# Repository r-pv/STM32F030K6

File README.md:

# rSTM32F030K6 ProMini

An ST development board based on the rSTM32F030K6T6/rSTM32F030K6 (Clock: 48MHz, flash: 32Kb, Ram:4Kb) MCU (LQFP-32) compatible with STM32Duino (Arduino).

## Install

**Update:** STCore v2.0 includes support for this MCU, if you're using STCore v2.0 you don't need to install anything.

- This requires the [STM32 core for arduino](https://github.com/stm32duino/Arduino_Core_STM32/), the ST original.
- I used this [guide to add the board](https://github.com/stm32duino/wiki/wiki/Add-a-new-variant-(board)), you can check it or continue with my suggestions to install the new board.
- Copy the **"DEMO_F030K6"** folder to the Arduino **"variants"** folder, in win7 is located at: **c:\Users\\<USERNAME\>\AppData\Local\Arduino15\packages\STM32\hardware\stm32\1.6.1\variants**
- Edit the **"boards.txt"** file, in win7 is located at a lever up than the "variants" folder, search for the **F030F4** board and add the lines to leave as I show you next:
```
# DEMO_F030F4 board
# Support: Serial1 (USART1 on PA3, PA2)
GenF0.menu.pnum.DEMO_F030F4=STM32F030F4 Demo board
GenF0.menu.pnum.DEMO_F030F4.upload.maximum_data_size=4096
GenF0.menu.pnum.DEMO_F030F4.upload.maximum_size=16384
GenF0.menu.pnum.DEMO_F030F4.build.mcu=cortex-m0
GenF0.menu.pnum.DEMO_F030F4.build.board=DEMO_F030F4
GenF0.menu.pnum.DEMO_F030F4.build.series=STM32F0xx
GenF0.menu.pnum.DEMO_F030F4.build.product_line=STM32F030x6
GenF0.menu.pnum.DEMO_F030F4.build.variant=DEMO_F030F4
GenF0.menu.pnum.DEMO_F030F4.build.cmsis_lib_gcc=arm_cortexM0l_math

# DEMO_F030K6 board
# Support: Serial1 (USART1 on PA3, PA2)
GenF0.menu.pnum.DEMO_F030K6=STM32F030K6 Demo board
GenF0.menu.pnum.DEMO_F030K6.upload.maximum_data_size=4096
GenF0.menu.pnum.DEMO_F030K6.upload.maximum_size=32768
GenF0.menu.pnum.DEMO_F030K6.build.mcu=cortex-m0
GenF0.menu.pnum.DEMO_F030K6.build.board=DEMO_F030K6
GenF0.menu.pnum.DEMO_F030K6.build.series=STM32F0xx
GenF0.menu.pnum.DEMO_F030K6.build.product_line=STM32F030x6
GenF0.menu.pnum.DEMO_F030K6.build.variant=DEMO_F030K6
GenF0.menu.pnum.DEMO_F030K6.build.cmsis_lib_gcc=arm_cortexM0l_math
```

## Files and Folders description

- **DEMO_F030K6** it's the variant board for the STM32 Arduino Core.
- **gerbers** it's the PCB gerbers.
- **rSTM32F030K6T6** it's the KiCAD 5.1.2 project.
- **Schematic.pdf** as in the name.

## Running some tests

## Reducing the size of your sketch

For some reason it seems that the sketchs for this platform gets way too fat (relative to standard arduino-atmel sketch sizes) and on some cases won't fit well on our board, a way to fit the sketchs to the flash/ram size that this board has it's to create a file **hal_conf_extra.h** on the sketch folder and disabling all features that weren't using:

```
#define HAL_ADC_MODULE_DISABLED
#define HAL_I2C_MODULE_DISABLED
#define HAL_RTC_MODULE_DISABLED
#define HAL_SPI_MODULE_DISABLED
#define HAL_TIM_MODULE_DISABLED
#define HAL_DAC_MODULE_DISABLED
#define HAL_EXTI_MODULE_DISABLED
#define HAL_ETH_MODULE_DISABLED
#define HAL_SD_MODULE_DISABLED
#define HAL_QSPI_MODULE_DISABLED
```
_(an arduino restart may be required on changes to this file)._

Also, if you aren't using the serial you cand disable it on the arduino menu:

**Board > U(S)ART Support > Disabled.**

## Notes

This it's the first board variant I made, so errors may occur.

[STM32Duino thread.](http://www.stm32duino.com/viewtopic.php?f=30&p=55201)

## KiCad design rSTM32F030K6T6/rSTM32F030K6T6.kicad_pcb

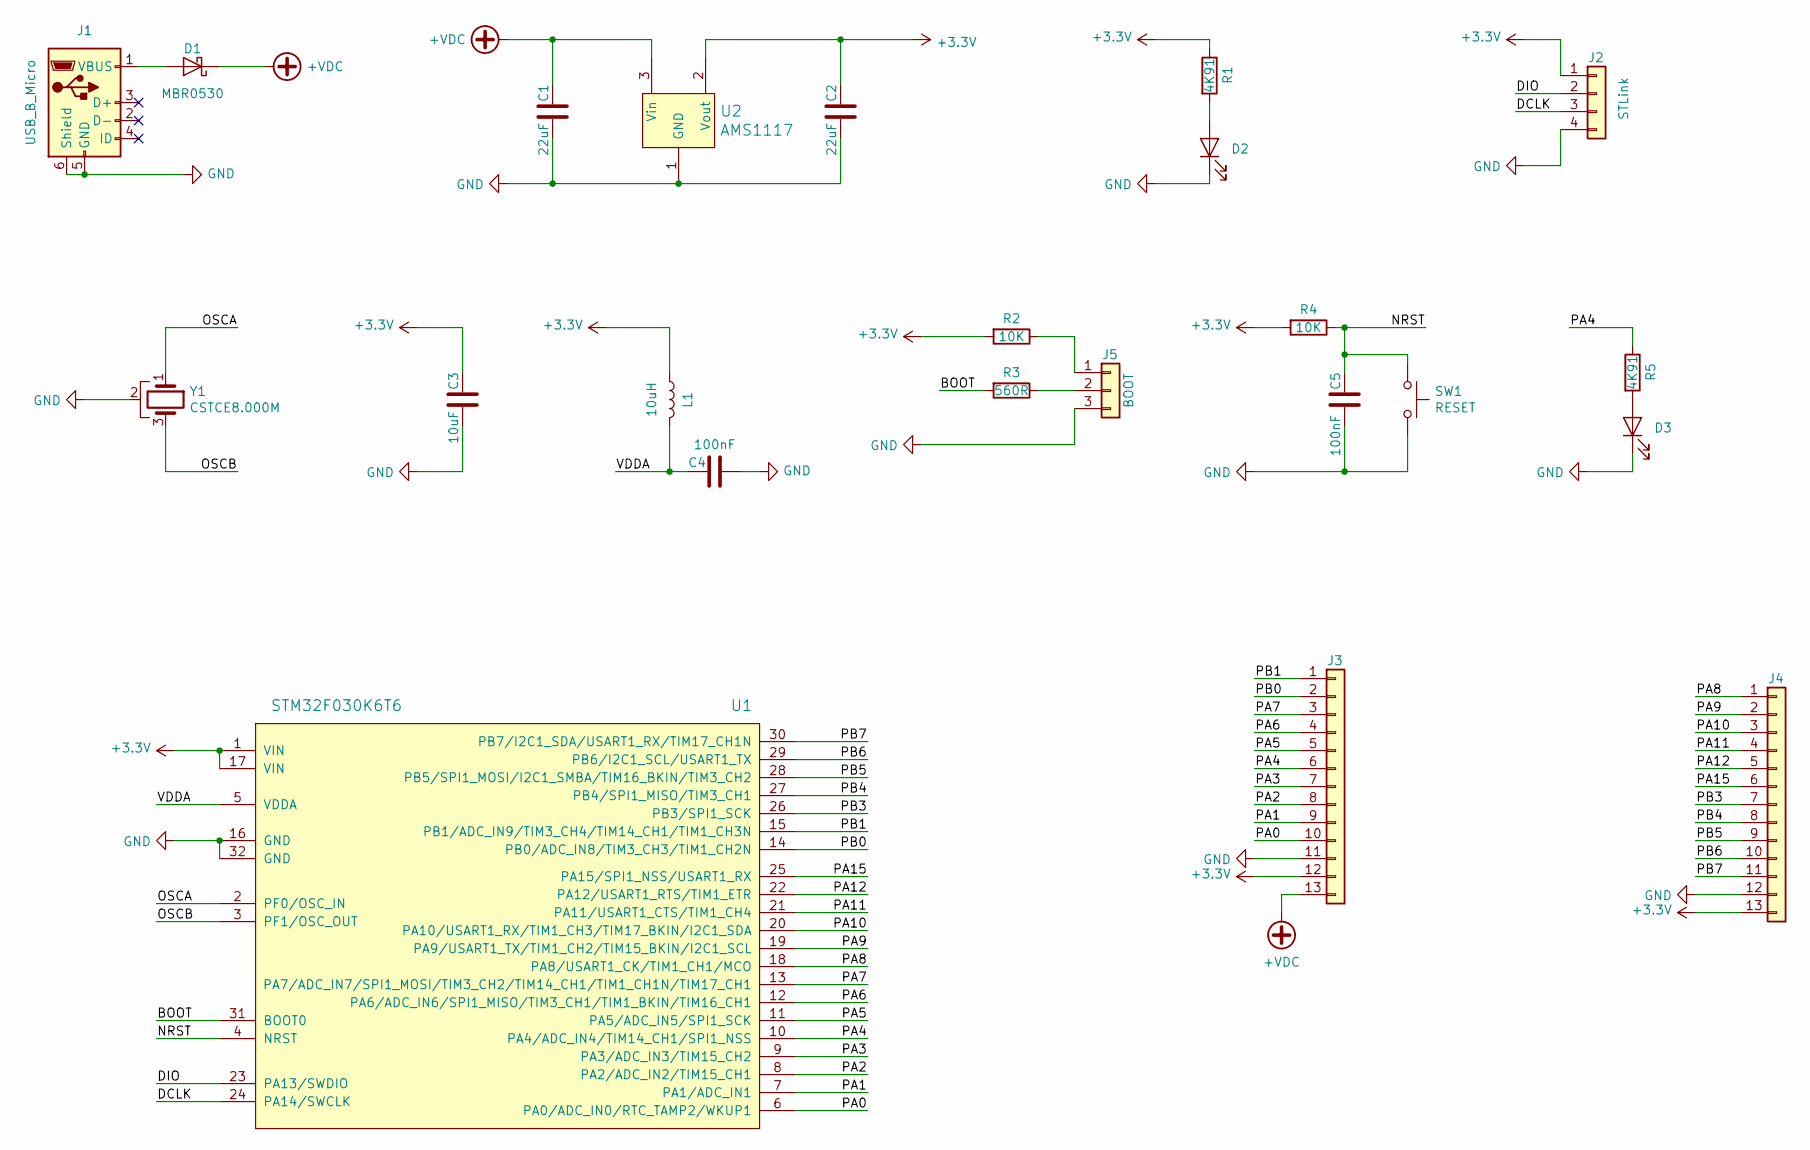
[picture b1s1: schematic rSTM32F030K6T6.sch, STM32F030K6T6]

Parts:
C1, C2: 22uF; C_0805
C3: 10uF; C_0805
C4, C5: 100nF; C_0805
D1: MBR0530; D_SOD-123
D2, D3: LED; LED_0805
J1: USB_B_Micro; USB_Micro-B_Molex_47346-0001
J2: STLink; Pin_Header_Straight_1x04_Pitch2.54mm
J3, J4: Pin_Header_Straight_1x13_Pitch2.54mm
J5: BOOT; Pin_Header_Straight_1x03_Pitch2.54mm
L1: 10uH; L_0805
R1, R5: 4K91; R_0603
R2, R4: 10K; R_0603
R3: 560R; R_0603
SW1: RESET; SW_SPST_EVPBF
U1: STM32F030K6T6; LQFP-32_7x7mm_Pitch0.8mm
U2: AMS1117; SOT-223-3_TabPin2
Y1: CSTCE8.000M; Crystal_CSTCE_3pin_3.2x1.3

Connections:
+3V3: C2.1, C3.1, J2.1, J3.12, J4.13, L1.1, R1.1, R2.2, R4.2, U1.1 (VIN), U1.17 (VIN), U2.2 (Vout)
+VDC: C1.1, D1.1 (K), J3.13, U2.3 (Vin)
/BOOT: R3.2, U1.31 (BOOT0)
/DCLK: J2.3, U1.24 (PA14/SWCLK)
/DIO: J2.2, U1.23 (PA13/SWDIO)
/NRST: C5.1, R4.1, SW1.1, U1.4 (NRST)
/OSCA: U1.2 (PF0/OSC_IN), Y1.1
/OSCB: U1.3 (PF1/OSC_OUT), Y1.3
/PA0: J3.10, U1.6 (PA0/ADC_IN0/RTC_TAMP2/WKUP1)
/PA1: J3.9, U1.7 (PA1/ADC_IN1)
/PA2: J3.8, U1.8 (PA2/ADC_IN2/TIM15_CH1)
/PA3: J3.7, U1.9 (PA3/ADC_IN3/TIM15_CH2)
/PA4: J3.6, R5.1, U1.10 (PA4/ADC_IN4/TIM14_CH1/SPI1_NSS)
/PA5: J3.5, U1.11 (PA5/ADC_IN5/SPI1_SCK)
/PA6: J3.4, U1.12 (PA6/ADC_IN6/SPI1_MISO/TIM3_CH1/TIM1_BKI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)
/PA7: J3.3, U1.13 (PA7/ADC_IN7/SPI1_MOSI/TIM3_CH2/TIM14_CH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)
/PA8: J4.1, U1.18 (PA8/USART1_CK/TIM1_CH1/MCO)
/PA9: J4.2, U1.19 (PA9/USART1_TX/TIM1_CH2/TIM15_BKIN/I2C1_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)
/PA10: J4.3, U1.20 (PA10/USART1_RX/TIM1_CH3/TIM17_BKIN/I2C1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)
/PA11: J4.4, U1.21 (PA11/USART1_CTS/TIM1_CH4)
/PA12: J4.5, U1.22 (PA12/USART1_RTS/TIM1_ETR)
/PA15: J4.6, U1.25 (PA15/SPI1_NSS/USART1_RX)
/PB0: J3.2, U1.14 (PB0/ADC_IN8/TIM3_CH3/TIM1_CH2N)
/PB1: J3.1, U1.15 (PB1/ADC_IN9/TIM3_CH4/TIM14_CH1/TIM1_CH3N)
/PB3: J4.7, U1.26 (PB3/SPI1_SCK)
/PB4: J4.8, U1.27 (PB4/SPI1_MISO/TIM3_CH1)
/PB5: J4.9, U1.28 (PB5/SPI1_MOSI/I2C1_SMBA/TIM16_BKIN/TIM3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)
/PB6: J4.10, U1.29 (PB6/I2C1_SCL/USART1_TX)
/PB7: J4.11, U1.30 (PB7/I2C1_SDA/USART1_RX/TIM17_CH1N)
/VDDA: C4.2, L1.2, U1.5 (VDDA)
GND: C1.2, C2.2, C3.2, C4.1, C5.2, D2.1 (K), D3.1 (K), J1.5 (GND), J1.6 (Shield), J2.4, J3.11, J4.12, J5.3, SW1.2, U1.16 (GND), U1.32 (GND), U2.1 (GND), Y1.2
unnamed: D1.2 (A), J1.1 (VBUS)
unnamed: D2.2 (A), R1.2
unnamed: D3.2 (A), R5.2
unnamed: J5.1, R2.1
unnamed: J5.2, R3.1

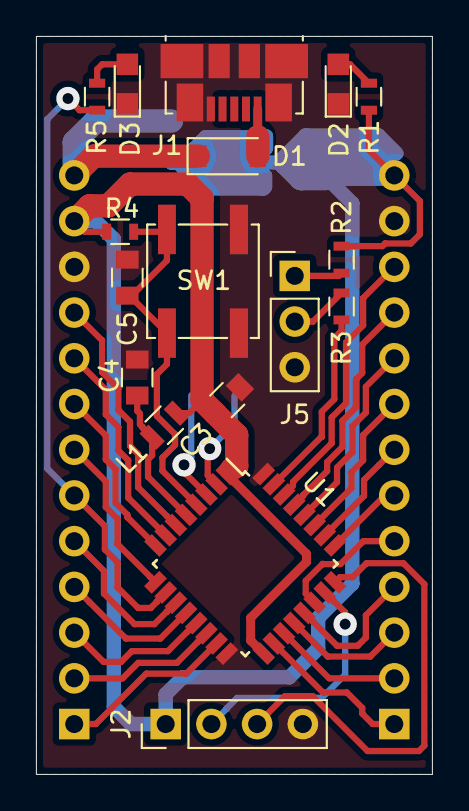
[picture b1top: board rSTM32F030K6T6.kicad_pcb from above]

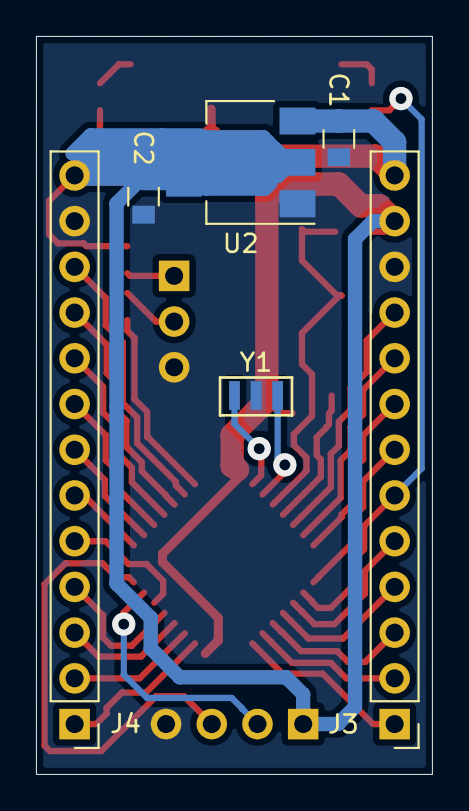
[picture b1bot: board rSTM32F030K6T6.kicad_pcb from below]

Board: 2 copper layers, 22.0 x 41.0 mm, 23 parts (6 on the bottom side), 36 nets.

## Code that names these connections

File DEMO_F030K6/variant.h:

/*
 *******************************************************************************
 * Copyright (c) 2017, STMicroelectronics
 * All rights reserved.
 *
 * Redistribution and use in source and binary forms, with or without
 * modification, are permitted provided that the following conditions are met:
 *
 * 1. Redistributions of source code must retain the above copyright notice,
 *    this list of conditions and the following disclaimer.
 * 2. Redistributions in binary form must reproduce the above copyright notice,
 *    this list of conditions and the following disclaimer in the documentation
 *    and/or other materials provided with the distribution.
 * 3. Neither the name of STMicroelectronics nor the names of its contributors
 *    may be used to endorse or promote products derived from this software
 *    without specific prior written permission.
 *
 * THIS SOFTWARE IS PROVIDED BY THE COPYRIGHT HOLDERS AND CONTRIBUTORS "AS IS"
 * AND ANY EXPRESS OR IMPLIED WARRANTIES, INCLUDING, BUT NOT LIMITED TO, THE
 * IMPLIED WARRANTIES OF MERCHANTABILITY AND FITNESS FOR A PARTICULAR PURPOSE ARE
 * DISCLAIMED. IN NO EVENT SHALL THE COPYRIGHT HOLDER OR CONTRIBUTORS BE LIABLE
 * FOR ANY DIRECT, INDIRECT, INCIDENTAL, SPECIAL, EXEMPLARY, OR CONSEQUENTIAL
 * DAMAGES (INCLUDING, BUT NOT LIMITED TO, PROCUREMENT OF SUBSTITUTE GOODS OR
 * SERVICES; LOSS OF USE, DATA, OR PROFITS; OR BUSINESS INTERRUPTION) HOWEVER
 * CAUSED AND ON ANY THEORY OF LIABILITY, WHETHER IN CONTRACT, STRICT LIABILITY,
 * OR TORT (INCLUDING NEGLIGENCE OR OTHERWISE) ARISING IN ANY WAY OUT OF THE USE
 * OF THIS SOFTWARE, EVEN IF ADVISED OF THE POSSIBILITY OF SUCH DAMAGE.
 *******************************************************************************
 */
#ifndef _VARIANT_ARDUINO_STM32_
#define _VARIANT_ARDUINO_STM32_

/*----------------------------------------------------------------------------
 *        Headers
 *----------------------------------------------------------------------------*/
#ifdef __cplusplus
extern "C"{
#endif // __cplusplus

/*----------------------------------------------------------------------------
 *        Pins
 *----------------------------------------------------------------------------*/
// USB connector on the top, MCU side
// Left.Side
#define PA0  0  //D0/A0
#define PA1  1  //D1/A1
#define PA2  2  //D2/A2 - TX
#define PA3  3  //D3/A3 - RX
#define PA4  4  //D4/A4 - LED
#define PA5  5  //D5/A5 - SCK
#define PA6  6  //D6/A6 - MISO
#define PA7  7  //D7/A7 - MOSI
#define PB0  8  //D8/A8 - SS
#define PB1  9  //D9/A8 - 
// Bottom.side
#define PA13 10 //D10   - SWDIO
#define PA14 11 //D11   - SWCLK
// Right.side
#define PA8  12 //D12  -
#define PA9  13 //D13  - 
#define PA10 14 //D14  - 
#define PA11 15 //D15  - 
#define PA12 16 //D16  - 
#define PA15 17 //D17  - 
#define PB3  18 //D18  - 
#define PB4  19 //D19  - 
#define PB5  20 //D20  - 
#define PB6  21 //D21  - 
#define PB7  22 //D22  - 

// Define pin names to match digital pin number --> Dx
// It could be used with preprocessor tests (e.g. #if PXn == 3)
// so an enum will not work.
// !!!
// !!! Copy the digitalPin[] array from the variant.cpp
// !!! and remove all '_': PX_n --> PXn
// !!! For NC, comment the line to warn x pin number is NC
// !!! // x is NC
// !!! For duplicated pin name, comment the line to warn x pin number
// !!! is PXn which is already defined with y pin number
// !!! // x is PXn (y)
// !!! Ex:
// !!! ...
// !!! #define PA4  20 // A14
// !!! #define PB4  21
// !!! #define PB5  22
// !!! #define PB3  23
// !!! // 24 is PA4 (20)
// !!! // 25 is PB4 (21)
// !!! #define PA2  26 // A15
// !!! ...
//#define PXn x

// This must be a literal
// It is used with preprocessor tests (e.g. #if NUM_DIGITAL_PINS > 3)
// so an enum will not work.
#define NUM_DIGITAL_PINS        32

// Allow to define Arduino style alias for analog input pin number --> Ax
// All pins are digital, analog inputs are a subset of digital pins
// and must be contiguous to be able to loop on each value
// This must be a literal with a value less than or equal to MAX_ANALOG_INPUTS
// defined in pin_arduino.h
// It is used with preprocessor tests (e.g. #if NUM_ANALOG_INPUTS > 3)
// so an enum will not work.
// !!!
// !!! It must be aligned with the number of analog PinName
// !!! defined in digitalPin[] array in variant.cpp
// !!!
#define NUM_ANALOG_INPUTS       10
// Define digital pin number of the first analog input  (i.e. which digital pin is A0)
// First analog pin value (A0) must be greater than or equal to NUM_ANALOG_INPUTS
#define NUM_ANALOG_FIRST        23

// Below ADC, DAC and PWM definitions already done in the core
// Could be redefined here if needed
// ADC resolution is 12bits
//#define ADC_RESOLUTION          12
//#define DACC_RESOLUTION         12

// PWM resolution
//#define PWM_RESOLUTION          8
//#define PWM_FREQUENCY           1000
//#define PWM_MAX_DUTY_CYCLE      255

// On-board LED pin number
#define LED_BUILTIN             PA4
#define LED_GREEN               LED_BUILTIN

// On-board user button
#define USER_BTN                x

// Below SPI and I2C definitions already done in the core
// Could be redefined here if differs from the default one
// SPI Definitions
// SPI Definitions
#define PIN_SPI_SS              PB0
#define PIN_SPI_MOSI            PA7
#define PIN_SPI_MISO            PA6
#define PIN_SPI_SCK             PA5

// I2C Definitions
#define PIN_WIRE_SDA            PA10 // Default for Arduino connector compatibility
#define PIN_WIRE_SCL            PA9  // Default for Arduino connector compatibility

// Timer Definitions
// Do not use timer used by PWM pins when possible. See PinMap_PWM.
#define TIMER_TONE              TIM17

// Do not use basic timer: OC is required
#define TIMER_SERVO             TIM16  //TODO: advanced-control timers don't work

// UART Definitions
#define SERIAL_UART_INSTANCE    1
// Default pin used for 'Serial' instance
// Mandatory for Firmata
#define PIN_SERIAL_RX           PA3
#define PIN_SERIAL_TX           PA2

// UART Definitions
// Define here Serial instance number to map on Serial generic name
//#define SERIAL_UART_INSTANCE    x //ex: 2 for Serial2 (USART2)
// DEBUG_UART could be redefined to print on another instance than 'Serial'
//#define DEBUG_UART              ((USART_TypeDef *) U(S)ARTX) // ex: USART3
// DEBUG_UART baudrate, default: 9600 if not defined
//#define DEBUG_UART_BAUDRATE     x
// DEBUG_UART Tx pin name, default: the first one found in PinMap_UART_TX for DEBUG_UART
//#define DEBUG_PINNAME_TX        PX_n // PinName used for TX


// Optional PIN_SERIALn_RX and PIN_SERIALn_TX where 'n' is the U(S)ART number
// Used when user instanciate a hardware Serial using its peripheral name.
// Example: HardwareSerial mySerial(USART3);
// will use PIN_SERIAL3_RX and PIN_SERIAL3_TX if defined.
//#define PIN_SERIALn_RX          x // For U(S)ARTn RX
//#define PIN_SERIALn_TX          x // For U(S)ARTn TX
//#define PIN_SERIALLP1_RX        x // For LPUART1 RX
//#define PIN_SERIALLP1_TX        x // For LPUART1 TX

// SD card slot Definitions
// SD detect signal can be defined if required
//#define SD_DETECT_PIN           x
// SD Read/Write timeout, default value defined in STM32SD library
//#define SD_DATATIMEOUT          x

#ifdef __cplusplus
} // extern "C"
#endif
/*----------------------------------------------------------------------------
 *        Arduino objects - C++ only
 *----------------------------------------------------------------------------*/

#ifdef __cplusplus
// These serial port names are intended to allow libraries and architecture-neutral
// sketches to automatically default to the correct port name for a particular type
// of use.  For example, a GPS module would normally connect to SERIAL_PORT_HARDWARE_OPEN,
// the first hardware serial port whose RX/TX pins are not dedicated to another use.
//
// SERIAL_PORT_MONITOR        Port which normally prints to the Arduino Serial Monitor
//
// SERIAL_PORT_USBVIRTUAL     Port which is USB virtual serial
//
// SERIAL_PORT_LINUXBRIDGE    Port which connects to a Linux system via Bridge library
//
// SERIAL_PORT_HARDWARE       Hardware serial port, physical RX & TX pins.
//
// SERIAL_PORT_HARDWARE_OPEN  Hardware serial ports which are open for use.  Their RX & TX
//                            pins are NOT connected to anything by default.
#define SERIAL_PORT_MONITOR     Serial
#define SERIAL_PORT_HARDWARE    Serial
#endif

#endif /* _VARIANT_ARDUINO_STM32_ */

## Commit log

2019-07-23 Added I2C and SPI pins
2019-07-24 Changes to work with 1.6.1 Core
    When I made this variant I was using 1.5 STM32 Core, now I've upgraded to 1.6.1 and the variant didn't work anymore so changes were needed.
2019-08-03 Added RX/TX pins.
2019-08-03 Added extra info.
2019-09-12 small fix.
2019-09-23 Pinout update: added ADC and PWM pins.
2019-10-24 Fixed a bug with the analogs.
    Fixed a mistake I made.
2021-05-03 ST Core v2.0 notice.
